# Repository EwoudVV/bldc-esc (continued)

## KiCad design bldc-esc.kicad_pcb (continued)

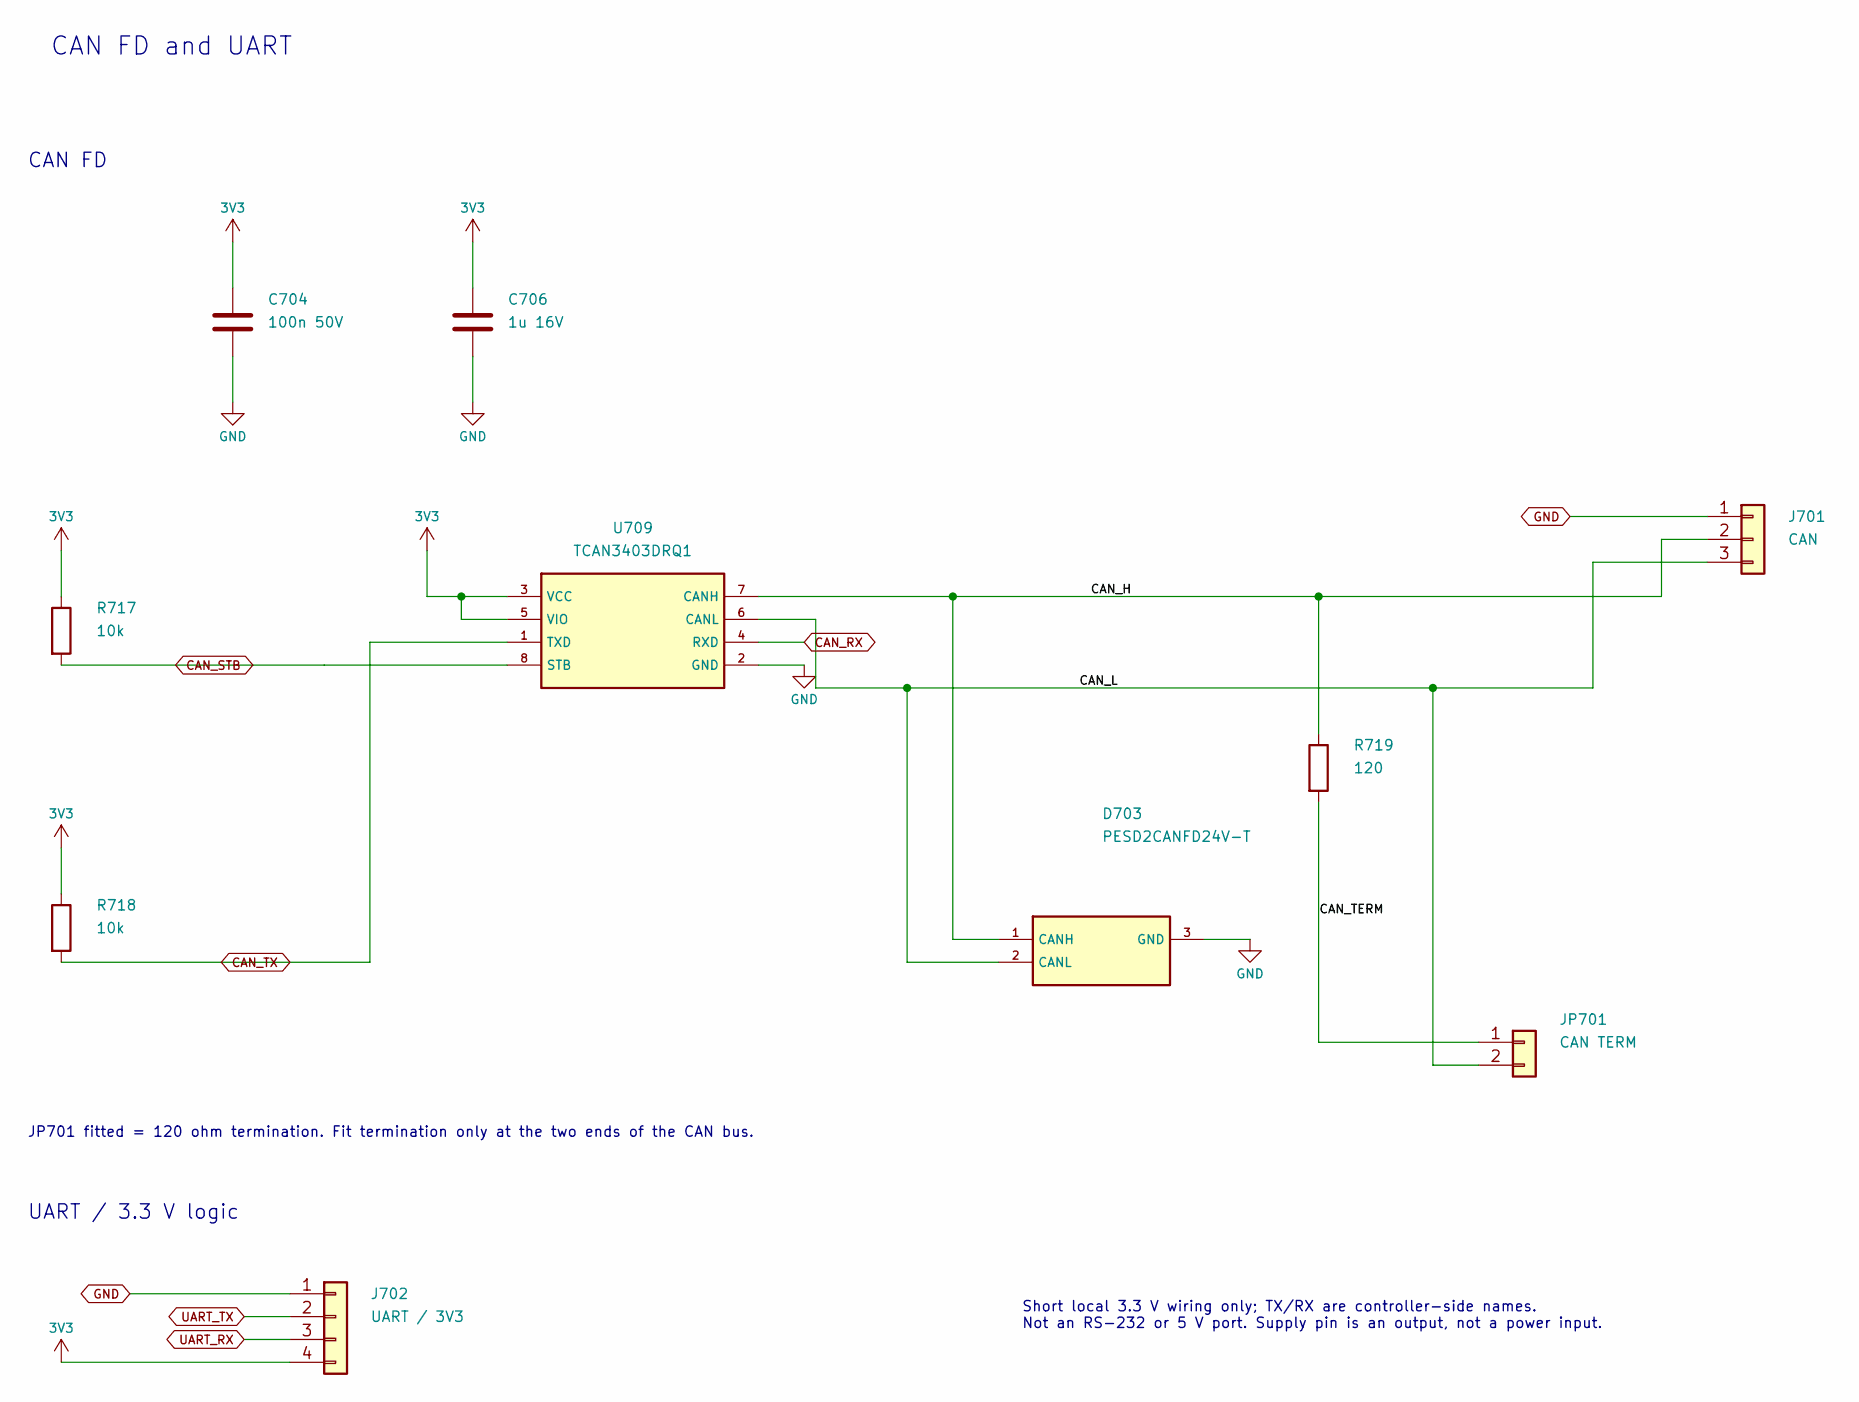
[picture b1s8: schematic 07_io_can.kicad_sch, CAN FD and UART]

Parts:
C704: 100n 50V; C_0603_1608Metric; MPN C0603C104K5RACTU
C706: 1u 16V; C_0603_1608Metric; MPN C0603C105K4RACTU
D703: PESD2CANFD24V-T; SOT-23; MPN PESD2CANFD24V-TR
J701: CAN; JST_GH_BM03B-GHS-TBT_1x03-1MP_P1.25mm_Vertical; MPN BM03B-GHS-TBT(LF)(SN)
J702: UART / 3V3; JST_GH_BM04B-GHS-TBT_1x04-1MP_P1.25mm_Vertical; MPN BM04B-GHS-TBT(LF)(SN)
JP701: CAN TERM; PinHeader_1x02_P2.54mm_Vertical; MPN M20-9990245
R717, R718: 10k; R_0603_1608Metric; MPN RC0603FR-0710KL
R719: 120; R_0805_2012Metric; MPN RC0805FR-07120RL
U709: TCAN3403DRQ1; SOIC-8_3.9x4.9mm_P1.27mm; MPN TCAN3403DRQ1

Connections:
3V3: C704.1, C706.1, J702.4, R717.1, R718.1, U709.3 (VCC), U709.5 (VIO); also elsewhere on the board
/07_io_can/CAN_H: D703.1 (CANH), J701.2, R719.1, U709.7 (CANH)
/07_io_can/CAN_L: D703.2 (CANL), J701.3, JP701.2, U709.6 (CANL)
/07_io_can/CAN_TERM: JP701.1, R719.2
CAN_RX: U709.4 (RXD); also elsewhere on the board
CAN_STB: R717.2, U709.8 (STB); also elsewhere on the board
CAN_TX: R718.2, U709.1 (TXD); also elsewhere on the board
UART_RX: J702.3; also elsewhere on the board
UART_TX: J702.2; also elsewhere on the board

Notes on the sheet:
CAN FD and UART
CAN FD
JP701 fitted = 120 ohm termination. Fit termination only at the two ends of the CAN bus.
UART / 3.3 V logic
Short local 3.3 V wiring only; TX/RX are controller-side names. Not an RS-232 or 5 V port. Supply pin is an output, not a power input.

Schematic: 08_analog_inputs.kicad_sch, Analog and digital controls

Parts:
C845, C847: 100n 50V; C_0603_1608Metric; MPN C0603C104K5RACTU
C850, C855: 10n 50V; C_0603_1608Metric; MPN C0603C103K5RACTU
C852, C857, C865, C868, C871: 1n 50V; C_0603_1608Metric; MPN C0603C102J5GACTU
D850, D855: BAV199; SOT-23; MPN BAV199,215
D852, D857, D865, D868, D871: PESD5V0S1BA; D_SOD-323; MPN PESD5V0S1BA,115
J801: THROTTLE_ADC; JST_GH_BM03B-GHS-TBT_1x03-1MP_P1.25mm_Vertical; MPN BM03B-GHS-TBT(LF)(SN)
J802: AUX_ANALOG_ADC; JST_GH_BM03B-GHS-TBT_1x03-1MP_P1.25mm_Vertical; MPN BM03B-GHS-TBT(LF)(SN)
J803: RC PWM; JST_GH_BM03B-GHS-TBT_1x03-1MP_P1.25mm_Vertical; MPN BM03B-GHS-TBT(LF)(SN)
J804: BRAKE / DIR; JST_GH_BM03B-GHS-TBT_1x03-1MP_P1.25mm_Vertical; MPN BM03B-GHS-TBT(LF)(SN)
R850, R855: 12.1k; R_0603_1608Metric; MPN RC0603FR-0712K1L
R851, R856, R866, R869, R872: 10k; R_0603_1608Metric; MPN RC0603FR-0710KL
R852, R857: 100; R_0603_1608Metric; MPN RC0603FR-07100RL
R865, R868, R871: 1k; R_0603_1608Metric; MPN RC0603FR-071KL
U802: SN74LVC3G17DCTR; SSOP-8_2.95x2.8mm_P0.65mm; MPN SN74LVC3G17DCTR
U803: TLV9062IDR; SOIC-8_3.9x4.9mm_P1.27mm; MPN TLV9062IDR

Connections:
3V3: C845.1, R869.1, R872.1, U802.8 (VCC); also elsewhere on the board
3V3_A: C847.1, D850.2 (K), D855.2 (K), U803.8 (V+); also elsewhere on the board
5V_HALL: J801.1, J802.1, J803.2; also elsewhere on the board
/08_analog_inputs/AUX_ANALOG_ADC_BUF: R857.1, U803.6 (-), U803.7
/08_analog_inputs/AUX_ANALOG_ADC_DIV: C855.1, D855.3 (common), R855.2, R856.1, U803.5 (+)
/08_analog_inputs/RC_PWM_RAW_FILT: C865.1, R865.2, U802.1
/08_analog_inputs/THROTTLE_ADC_BUF: R852.1, U803.1, U803.2 (-)
/08_analog_inputs/THROTTLE_ADC_DIV: C850.1, D850.3 (common), R850.2, R851.1, U803.3 (+)
/08_analog_inputs/nBRAKE_RAW_FILT: C868.1, R868.2, U802.3
/08_analog_inputs/nDIR_RAW_FILT: C871.1, R871.2, U802.6
AUX_ANALOG_ADC: C857.1, R857.2; also elsewhere on the board
RC_PWM_IN: U802.7; also elsewhere on the board
THROTTLE_ADC: C852.1, R852.2; also elsewhere on the board
nBRAKE_IN: U802.5; also elsewhere on the board
nDIR_IN: U802.2; also elsewhere on the board

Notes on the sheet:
Analog and digital controls
Analog controls / 0-5 V input
Digital controls / 3.3 or 5 V logic

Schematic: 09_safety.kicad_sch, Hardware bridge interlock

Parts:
C711, C712, C713, C714, C715, C716, C719, C720: 100n 50V; C_0603_1608Metric; MPN C0603C104K5RACTU
R705, R707, R708, R716, R724, R725: 100k; R_0603_1608Metric; MPN RC0603FR-07100KL
R706, R710, R711, R712, R713, R714, R715, R723: 10k; R_0603_1608Metric; MPN RC0603FR-0710KL
R709: 1k; R_0603_1608Metric; MPN RC0603FR-071KL
U703, U704, U707, U708, U711, U712: SN74LVC1G11DBVR; SOT-23-6; MPN SN74LVC1G11DBVR
U705: SN74LVC1G74DCTR; SSOP-8_2.95x2.8mm_P0.65mm; MPN SN74LVC1G74DCTR
U706: SN74LVC244APWR; TSSOP-20_4.4x6.5mm_P0.65mm; MPN SN74LVC244APWR

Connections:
3V3: C711.1, C712.1, C713.1, C714.1, C715.1, C716.1, C719.1, C720.1, R706.1, U703.5 (VCC), U704.5 (VCC), U705.2 (D), U705.7 (nPRE), U705.8 (VCC), U706.20 (VCC), U707.5 (VCC), U708.5 (VCC), U711.5 (VCC), U712.5 (VCC); also elsewhere on the board
/09_safety/DRV_ENABLE_PRE: U707.4, U712.1
/09_safety/SAFETY_GOOD: U704.4, U705.6 (nCLR)
/09_safety/SYSTEM_GOOD: U704.1, U711.4
/09_safety/SYSTEM_GOOD_PRE: U703.4, U711.1
/09_safety/nFAULT_LATCH: R709.1, U705.5 (Q), U708.6
/09_safety/nPWM_ENABLE: R706.2, U705.3 (nQ), U706.1 (nOE1), U706.19 (nOE2)
BRIDGE_ARM_REQ: R705.1, U705.1 (CLK); also elsewhere on the board
BRK_ARMED: U711.6, U712.6; also elsewhere on the board
BUS_OK: R708.1, U703.3, U707.6; also elsewhere on the board
BUS_OK_SENSE: R708.2; also elsewhere on the board
DRV_ENABLE: U712.4; also elsewhere on the board
DRV_WAKE_REQ: R716.1, U707.1; also elsewhere on the board
DRV_nFAULT: R725.1, U704.6; also elsewhere on the board
DRV_nFAULT_SENSE: R725.2; also elsewhere on the board
DUMP_PWM: U708.1; also elsewhere on the board
DUMP_PWM_SAFE: U708.4; also elsewhere on the board
HW_ENABLE_OK: U703.6; also elsewhere on the board
IN_AH: R710.1, U706.18 (Y1); also elsewhere on the board
IN_AL: R711.1, U706.16 (Y2); also elsewhere on the board
IN_BH: R712.1, U706.14 (Y3); also elsewhere on the board
IN_BL: R713.1, U706.12 (Y4); also elsewhere on the board
IN_CH: R714.1, U706.9 (Y5); also elsewhere on the board
IN_CL: R715.1, U706.7 (Y6); also elsewhere on the board
NRST: U703.1, U707.3, U708.3; also elsewhere on the board
PWM_AH: U706.2 (A1); also elsewhere on the board
PWM_AL: U706.4 (A2); also elsewhere on the board
PWM_BH: U706.6 (A3); also elsewhere on the board
PWM_BL: U706.8 (A4); also elsewhere on the board
PWM_CH: U706.11 (A5); also elsewhere on the board
PWM_CL: U706.13 (A6); also elsewhere on the board
WD_RUN: R723.1, U711.3, U712.3; also elsewhere on the board
WD_RUN_SENSE: R723.2; also elsewhere on the board
nFAULT_LATCH_SENSE: R709.2; also elsewhere on the board
nHW_ENABLE_FILT: R724.1; also elsewhere on the board
nHW_ENABLE_SENSE: R724.2; also elsewhere on the board
nOC_HW: R707.1, U704.3; also elsewhere on the board
nOC_HW_SENSE: R707.2; also elsewhere on the board

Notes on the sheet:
Hardware bridge interlock
Arm interlock / fault removal does not re-arm the bridge
Driver wake / independent chopper request
MCU monitoring / series isolation
Hardware fault and enable nodes are isolated from MCU GPIO drive. Disable UCPD dead-battery control before reading PB4.

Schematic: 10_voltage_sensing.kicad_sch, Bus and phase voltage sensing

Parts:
C801, C811, C821, C831: 220p 50V; C_0603_1608Metric; MPN C0603C221J5GACTU
C802, C812, C822, C832: 1n 50V; C_0603_1608Metric; MPN C0603C102J5GACTU
C840: 100n 50V; C_0603_1608Metric; MPN C0603C104K5RACTU
D801, D811, D821, D831: BAV199; SOT-23; MPN BAV199,215
R801, R802, R811, R812, R821, R822, R831, R832: 100k 0.1%; R_0603_1608Metric; MPN RT0603BRD07100KL
R803, R813, R823, R833: 10k 0.1%; R_0603_1608Metric; MPN RT0603BRD0710KL
R804, R814, R824, R834: 100; R_0603_1608Metric; MPN RC0603FR-07100RL
U801: TLV9064IPWR; TSSOP-14_4.4x5mm_P0.65mm; MPN TLV9064IPWR

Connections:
3V3_A: C840.1, D801.2 (K), D811.2 (K), D821.2 (K), D831.2 (K), U801.4 (V+); also elsewhere on the board
/10_voltage_sensing/V_BUS_ADC_BUF: R804.1, U801.1, U801.2 (-)
/10_voltage_sensing/V_BUS_ADC_DIV: C801.1, D801.3 (common), R802.2, R803.1, U801.3 (+)
/10_voltage_sensing/V_BUS_ADC_MID: R801.2, R802.1
/10_voltage_sensing/V_PHASE_A_BUF: R814.1, U801.6 (-), U801.7
/10_voltage_sensing/V_PHASE_A_DIV: C811.1, D811.3 (common), R812.2, R813.1, U801.5 (+)
/10_voltage_sensing/V_PHASE_A_MID: R811.2, R812.1
/10_voltage_sensing/V_PHASE_B_BUF: R824.1, U801.8, U801.9 (-)
/10_voltage_sensing/V_PHASE_B_DIV: C821.1, D821.3 (common), R822.2, R823.1, U801.10 (+)
/10_voltage_sensing/V_PHASE_B_MID: R821.2, R822.1
/10_voltage_sensing/V_PHASE_C_BUF: R834.1, U801.13 (-), U801.14
/10_voltage_sensing/V_PHASE_C_DIV: C831.1, D831.3 (common), R832.2, R833.1, U801.12 (+)
/10_voltage_sensing/V_PHASE_C_MID: R831.2, R832.1
PHASE_A: R811.1; also elsewhere on the board
PHASE_B: R821.1; also elsewhere on the board
PHASE_C: R831.1; also elsewhere on the board
VBUS: R801.1; also elsewhere on the board
V_BUS_ADC: C802.1, R804.2; also elsewhere on the board
V_PHASE_A: C812.1, R814.2; also elsewhere on the board
V_PHASE_B: C822.1, R824.2; also elsewhere on the board
V_PHASE_C: C832.1, R834.2; also elsewhere on the board

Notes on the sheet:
Bus and phase voltage sensing
Bus voltage
Phase A voltage
Phase B voltage
Phase C voltage
21:1 dividers; 2.5 V ADC full scale = 52.5 V at the input. Buffers isolate the dividers from ADC sampling transients. Normal operation remains limited to a 12-30 V bus.

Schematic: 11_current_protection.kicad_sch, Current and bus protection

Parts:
C110, C111, C112, C117: 10n 50V; C_0603_1608Metric; MPN C0603C103K5RACTU
C113, C114: 100n 50V; C_0603_1608Metric; MPN C0603C104K5RACTU
R110, R113, R114, R119: 10k 0.1%; R_0603_1608Metric; MPN RT0603BRD0710KL
R111, R112: 90.9k 0.1%; R_0603_1608Metric; MPN RT0603BRD0790K9L
R115: 16.9k 0.1%; R_0603_1608Metric; MPN RT0603BRD0716K9L
R116: 4.7k; R_0603_1608Metric; MPN RC0603FR-074K7L
R117: 10k; R_0603_1608Metric; MPN RC0603FR-0710KL
R118: 40.2k 0.1%; R_0603_1608Metric; MPN RT0603BRD0740K2L
U101, U102: TLV9024PWR; TSSOP-14_4.4x5mm_P0.65mm; MPN TLV9024PWR

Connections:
3V3: R116.1, R117.1; also elsewhere on the board
3V3_A: C113.1, C114.1, U101.3 (V+), U102.3 (V+); also elsewhere on the board
/11_current_protection/BUS_OV_REF: C112.1, R114.2, R115.1, U102.9 (+)
/11_current_protection/BUS_UV_REF: C117.1, R118.2, R119.1, U102.10 (-)
/11_current_protection/OC_HI: C110.1, R110.2, R111.1, U101.5 (+), U101.9 (+), U102.5 (+)
/11_current_protection/OC_LO: C111.1, R112.2, R113.1, U101.6 (-), U101.10 (-), U102.6 (-)
BUS_OK: R117.2, U102.13, U102.14; also elsewhere on the board
I_PHASE_A: U101.4 (-), U101.7 (+); also elsewhere on the board
I_PHASE_B: U101.8 (-), U101.11 (+); also elsewhere on the board
I_PHASE_C: U102.4 (-), U102.7 (+); also elsewhere on the board
VREF_2V5: R110.1, R112.1, R114.1, R118.1; also elsewhere on the board
V_BUS_ADC: U102.8 (-), U102.11 (+); also elsewhere on the board
nOC_HW: R116.2, U101.1, U101.2, U101.13, U101.14, U102.1, U102.2; also elsewhere on the board

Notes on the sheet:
Current and bus protection
Bipolar phase-current window
Phase A / upper
Phase A / lower
Phase B / upper
Phase B / lower
Phase C / upper
Phase C / lower
Current thresholds / about +/-50 A
Board protection only. Use lower motor limits. OEM motor: 0.75 A.
Bus window / about 10.5-33 V

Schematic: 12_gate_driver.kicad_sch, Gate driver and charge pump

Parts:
C201: 22u 63V; CP_Radial_D6.3mm_P2.50mm; MPN EEUFC1J220
C202: 100n 100V; C_0603_1608Metric; MPN C0603C104K1RACTU
C203: 47n 100V; C_0805_2012Metric; MPN C0805C473K1RACTU
C204: 1u 50V; C_1206_3216Metric; MPN C3216X7R1H105K160AB
C205: 1u 25V; C_0805_2012Metric; MPN C0805C105K3RACTU
C206: 1u 16V; C_0603_1608Metric; MPN C0603C105K4RACTU
C207: 100n 50V; C_0603_1608Metric; MPN C0603C104K5RACTU
R201: 2.2; R_0805_2012Metric; MPN RC0805FR-072R2L
R202: 4.7k; R_0603_1608Metric; MPN RC0603FR-074K7L
R203, R205: 10k; R_0603_1608Metric; MPN RC0603FR-0710KL
R204: 100k; R_0603_1608Metric; MPN RC0603FR-07100KL
U201: DRV8353SRTAT; DRV8353_RTA0040B; MPN DRV8353SRTAT

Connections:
3V3: R202.1, R203.1, R205.1; also elsewhere on the board
3V3_A: C207.1, U201.24 (VREF); also elsewhere on the board
/12_gate_driver/DRV_CPH: C203.1, U201.2 (CPH)
/12_gate_driver/DRV_CPL: C203.2, U201.1 (CPL)
/12_gate_driver/DRV_DVDD: C206.1, U201.38 (DVDD)
/12_gate_driver/DRV_VCP: C204.1, U201.5 (VCP)
/12_gate_driver/DRV_VGLS: C205.1, U201.40 (VGLS)
/12_gate_driver/DRV_VM: C201.1, C202.1, R201.2, U201.3 (VM)
DRV_ENABLE: R204.1, U201.31 (ENABLE); also elsewhere on the board
DRV_SCK: U201.29 (SCLK); also elsewhere on the board
DRV_SDI: U201.28 (SDI); also elsewhere on the board
DRV_SDO: R202.2, U201.27 (SDO); also elsewhere on the board
DRV_nCS: R205.2, U201.30 (nSCS); also elsewhere on the board
DRV_nFAULT: R203.2, U201.26 (nFAULT); also elsewhere on the board
GHA_DRV: U201.6 (GHA); also elsewhere on the board
GHB_DRV: U201.15 (GHB); also elsewhere on the board
GHC_DRV: U201.16 (GHC); also elsewhere on the board
GLA_DRV: U201.8 (GLA); also elsewhere on the board
GLB_DRV: U201.13 (GLB); also elsewhere on the board
GLC_DRV: U201.18 (GLC); also elsewhere on the board
IN_AH: U201.32 (INHA); also elsewhere on the board
IN_AL: U201.33 (INLA); also elsewhere on the board
IN_BH: U201.34 (INHB); also elsewhere on the board
IN_BL: U201.35 (INLB); also elsewhere on the board
IN_CH: U201.36 (INHC); also elsewhere on the board
IN_CL: U201.37 (INLC); also elsewhere on the board
KS_A_N: U201.10 (SNA); also elsewhere on the board
KS_B_N: U201.11 (SNB); also elsewhere on the board
KS_C_N: U201.20 (SNC); also elsewhere on the board
PHASE_A: U201.7 (SHA); also elsewhere on the board
PHASE_B: U201.14 (SHB); also elsewhere on the board
PHASE_C: U201.17 (SHC); also elsewhere on the board
SOURCE_A: U201.9 (SPA); also elsewhere on the board
SOURCE_B: U201.12 (SPB); also elsewhere on the board
SOURCE_C: U201.19 (SPC); also elsewhere on the board
SO_A_DRV: U201.23 (SOA); also elsewhere on the board
SO_B_DRV: U201.22 (SOB); also elsewhere on the board
SO_C_DRV: U201.21 (SOC); also elsewhere on the board
VBUS: C204.2, R201.1, U201.4 (VDRAIN); also elsewhere on the board

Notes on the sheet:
Gate driver and charge pump
Gate driver / charge pump
VM filter and pump capacitors belong next to U201. VCP reservoir returns to VBUS, not GND.
SPx returns directly to each low-side source. SNx / CSA inputs use Kelvin shunt sense pads.
Six PWM inputs arrive through the hardware arm interlock. ENABLE is separate for driver setup.

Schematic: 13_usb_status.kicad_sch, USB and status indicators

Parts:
C413: 100n 50V; C_0603_1608Metric; MPN C0603C104K5RACTU
D511: STATUS; LED_0603_1608Metric; MPN LTST-C190KGKT
D512: COMM; LED_0603_1608Metric; MPN LTST-C190KGKT
D513: POWER; LED_0603_1608Metric; MPN LTST-C190KGKT
F401: 0.5A / 6V; MF_PSMF0805; MPN MF-PSMF050X-2
J401: USB4105-GF-A; USB4105_PCBWay; MPN USB4105-GF-A
R411, R412: 5.1k; R_0603_1608Metric; MPN RC0603FR-075K1L
R413, R414: 22; R_0603_1608Metric; MPN RC0603FR-0722RL
R415: 10k; R_0603_1608Metric; MPN RC0603FR-0710KL
R416: 15k; R_0603_1608Metric; MPN RC0603FR-0715KL
R511, R512, R513: 1k; R_0603_1608Metric; MPN RC0603FR-071KL
TP401: 5V_BUS; TestPoint_Pad_D1.5mm; MPN TESTPOINT
TP402: 5V_SYS; TestPoint_Pad_D1.5mm; MPN TESTPOINT
TP403: 3V3; TestPoint_Pad_D1.5mm; MPN TESTPOINT
TP404: GND; TestPoint_Pad_D1.5mm; MPN TESTPOINT
U404: USBLC6-2SC6; SOT-23-6; MPN USBLC6-2SC6

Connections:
3V3: R513.1, TP403.1 (1_1); also elsewhere on the board
5V_BUS: TP401.1 (1_1); also elsewhere on the board
5V_SYS: TP402.1 (1_1); also elsewhere on the board
/13_usb_status/CC1: J401.A5 (CC1), R411.1
/13_usb_status/CC2: J401.B5 (CC2), R412.1
/13_usb_status/LED_1: D511.2 (A), R511.2
/13_usb_status/LED_2: D512.2 (A), R512.2
/13_usb_status/LED_3: D513.2 (A), R513.2
/13_usb_status/USB_DM_ESD: R414.1, U404.4 (I/O2)
/13_usb_status/USB_DM_PORT: J401.A7 (D-), J401.B7 (D-), U404.3 (I/O2)
/13_usb_status/USB_DP_ESD: R413.1, U404.6 (I/O1)
/13_usb_status/USB_DP_PORT: J401.A6 (D+), J401.B6 (D+), U404.1 (I/O1)
/13_usb_status/USB_VBUS_RAW: C413.1, F401.1, J401.A4 (VBUS), J401.A9 (VBUS), J401.B4 (VBUS), J401.B9 (VBUS), R415.1, U404.5 (VBUS)
CHASSIS: J401.SH (SHIELD); also elsewhere on the board
LED_COMM: R512.1; also elsewhere on the board
LED_STATUS: R511.1; also elsewhere on the board
USB_DM: R414.2; also elsewhere on the board
USB_DP: R413.2; also elsewhere on the board
USB_VBUS_SENSE: R415.2, R416.1; also elsewhere on the board

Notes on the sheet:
USB and status indicators
USB-C device port
Status / probe points
USB shield bonds to CHASSIS. D+/D- protection belongs close to the connector; 22 ohm resistors belong near the MCU.

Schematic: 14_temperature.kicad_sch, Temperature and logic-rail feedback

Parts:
C848: 100n 50V; C_0603_1608Metric; MPN C0603C104K5RACTU
C880, C883, C886, C889, C899: 10n 50V; C_0603_1608Metric; MPN C0603C103K5RACTU
C888, C891: 1n 50V; C_0603_1608Metric; MPN C0603C102J5GACTU
D886, D889: BAV199; SOT-23; MPN BAV199,215
D888, D891: PESD5V0S1BA; D_SOD-323; MPN PESD5V0S1BA,115
J805: NTC_MOTOR; JST_GH_BM02B-GHS-TBT_1x02-1MP_P1.25mm_Vertical; MPN BM02B-GHS-TBT(LF)(SN)
J806: NTC_DUMP; JST_GH_BM02B-GHS-TBT_1x02-1MP_P1.25mm_Vertical; MPN BM02B-GHS-TBT(LF)(SN)
R880, R883, R886, R889, R898, R899: 10k 0.1%; R_0603_1608Metric; MPN RT0603BRD0710KL
R887, R890: 1k; R_0603_1608Metric; MPN RC0603FR-071KL
R888, R891: 100; R_0603_1608Metric; MPN RC0603FR-07100RL
TH801, TH802: 10k / B25-50=3380K; R_0603_1608Metric; MPN NCP18XH103F03RB
U804: TLV9062IDR; SOIC-8_3.9x4.9mm_P1.27mm; MPN TLV9062IDR

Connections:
3V3: R898.1; also elsewhere on the board
3V3_A: C848.1, D886.2 (K), D889.2 (K), U804.8 (V+); also elsewhere on the board
/14_temperature/NTC_DUMP_BUF: R891.1, U804.6 (-), U804.7
/14_temperature/NTC_DUMP_DIV: C889.1, D889.3 (common), R889.2, R890.2, U804.5 (+)
/14_temperature/NTC_MOTOR_BUF: R888.1, U804.1, U804.2 (-)
/14_temperature/NTC_MOTOR_DIV: C886.1, D886.3 (common), R886.2, R887.2, U804.3 (+)
NTC_BRIDGE: C880.1, R880.2, TH801.1; also elsewhere on the board
NTC_DUMP: C891.1, R891.2; also elsewhere on the board
NTC_MOTOR: C888.1, R888.2; also elsewhere on the board
NTC_PCB: C883.1, R883.2, TH802.1; also elsewhere on the board
VREF_2V5: R880.1, R883.1, R886.1, R889.1; also elsewhere on the board
V_3V3_ADC: C899.1, R898.2, R899.1; also elsewhere on the board

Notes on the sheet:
Temperature and logic-rail feedback
Temperature feedback
TH801/TH802: 10k, B25/50=3380 K. External NTC conversion must subtract the 1k series resistor. External channels are buffered; configure their actual R/T curves before thermal-limit testing.

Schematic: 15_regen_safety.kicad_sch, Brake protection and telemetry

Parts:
C307, C309, C311: 100n 50V; C_0603_1608Metric; MPN C0603C104K5RACTU
C308: 1n 50V; C_0603_1608Metric; MPN C0603C102J5GACTU
C310: 10n 50V; C_0603_1608Metric; MPN C0603C103K5RACTU
C312: 100p 50V; C_0603_1608Metric; MPN C0603C101J5GACTU
D302, D303: BAT54H; D_SOD-123F; MPN BAT54H,115
R311, R312, R313: 10k; R_0603_1608Metric; MPN RC0603FR-0710KL
R314, R315, R317: 100k; R_0603_1608Metric; MPN RC0603FR-07100KL
R316, R318: 150k; R_0603_1608Metric; MPN RC0603FR-07150KL
R320: 10k 0.1%; R_0603_1608Metric; MPN RT0603BRD0710KL
R321: 15k 0.1%; R_0603_1608Metric; MPN RT0603BRD0715KL
U304: TLV3201AIDBVR; SOT-23-5; MPN TLV3201AIDBVR
U305: TPS3808G50DBVR; SOT-23-6; MPN TPS3808G50DBVR
U306: SN74LVC1G17DBVR; SOT-23-5; MPN SN74LVC1G17DBVR
U307: SN74LVC1G74DCTR; SSOP-8_2.95x2.8mm_P0.65mm; MPN SN74LVC1G74DCTR

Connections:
5V_BUS: C307.1, C309.1, C311.1, R311.1, R312.1, U304.5 (V+), U305.3 (nMR), U305.5 (SENSE), U305.6 (VDD), U306.5 (VCC), U307.2 (D), U307.7 (nPRE), U307.8 (VCC); also elsewhere on the board
/15_regen_safety/BRK_CLEAR: D302.2 (A), D303.2 (A), R311.2, U307.6 (nCLR)
/15_regen_safety/BRK_CLK: U306.4, U307.1 (CLK)
/15_regen_safety/BRK_CLK_RC: C310.1, R313.2, U306.2
/15_regen_safety/BRK_CT: C308.1, U305.4 (CT)
/15_regen_safety/BRK_OC_OK: D303.1 (K), U304.1 (OUT)
/15_regen_safety/BRK_POR: D302.1 (K), R312.2, R313.1, U305.1 (nRESET)
/15_regen_safety/nBRK_ARMED: R317.1, U307.3 (nQ)
BRK_ARMED: R314.1, U307.5 (Q); also elsewhere on the board
BRK_FAULT_SENSE: R317.2, R318.1; also elsewhere on the board
DUMP_ACTIVE_SENSE: R315.2, R316.1; also elsewhere on the board
DUMP_CURRENT: R320.1, U304.4 (IN-); also elsewhere on the board
DUMP_I_ADC: C312.1, R320.2, R321.1; also elsewhere on the board
DUMP_REF: U304.3 (IN+); also elsewhere on the board
nDUMP_REQUEST: R315.1; also elsewhere on the board

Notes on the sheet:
Brake protection and telemetry
5 V-to-3.3 V monitor dividers
Dump current: 36 mV/A to PA6 ADC2_IN3. Use a long regular ADC acquisition time.
Chopper overcurrent trip and power-cycle latch

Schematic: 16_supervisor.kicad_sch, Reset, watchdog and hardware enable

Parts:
C701, C703, C717, C718: 100n 50V; C_0603_1608Metric; MPN C0603C104K5RACTU
C702: 47n 50V; C_0603_1608Metric; MPN C0603C473K5RACTU
C705: 10n 50V; C_0603_1608Metric; MPN C0603C103K5RACTU
D704: PESD5V0S1BA; D_SOD-323; MPN PESD5V0S1BA,115
J703: HW ENABLE; PinHeader_1x02_P2.54mm_Vertical; MPN M20-9990245
JP704: RUN 1-2 / SERVICE 2-3; PinHeader_1x03_P2.54mm_Vertical; MPN M20-9990345
R701, R703: 0; R_0603_1608Metric; MPN RC0603JR-070RL
R702, R720, R722: 10k; R_0603_1608Metric; MPN RC0603FR-0710KL
R704: 100k; R_0603_1608Metric; MPN RC0603FR-07100KL
R721: 1k; R_0603_1608Metric; MPN RC0603FR-071KL
U701: TPS389033DSER; WSON-6_1.5x1.5mm_P0.5mm; MPN TPS389033DSER
U702: TPS3431SDRBR; VSON-8-1EP_3x3mm_P0.65mm_EP1.65x2.4mm; MPN TPS3431SDRBR
U710: SN74LVC1G14DBVR; SOT-23-5; MPN SN74LVC1G14DBVR

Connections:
3V3: C701.1, C703.1, C717.1, C718.1, JP704.1, R702.1, R720.1, R722.1, U701.3 (nMR), U701.4 (VDD), U702.1 (VDD), U702.3 (EN), U710.5 (VCC); also elsewhere on the board
3V3_A: U701.1 (SENSE); also elsewhere on the board
/16_supervisor/POR_CT: C702.1, U701.5 (CT)
/16_supervisor/POWER_OK: R701.2, U701.6 (nRESET)
/16_supervisor/WD_CWD: R702.2, U702.2 (CWD)
/16_supervisor/WD_OK: R703.2, U702.7 (nWDO)
HW_ENABLE_OK: U710.4; also elsewhere on the board
NRST: R701.1, R703.1; also elsewhere on the board
WD_HEARTBEAT: R704.1, U702.6 (WDI); also elsewhere on the board
WD_RUN: JP704.2, R722.2, U702.5 (SET1); also elsewhere on the board
nHW_ENABLE_FILT: C705.1, R721.2, U710.2; also elsewhere on the board

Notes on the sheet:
Reset, watchdog and hardware enable
Power-on reset and watchdog
Open-drain reset outputs share NRST through zero-ohm links. R504 on the MCU sheet provides the pull-up.
Service and hardware enable
RUN 1-2 / SERVICE 2-3. SERVICE or a chopper fault forces both driver-enable and bridge-arm paths off.

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
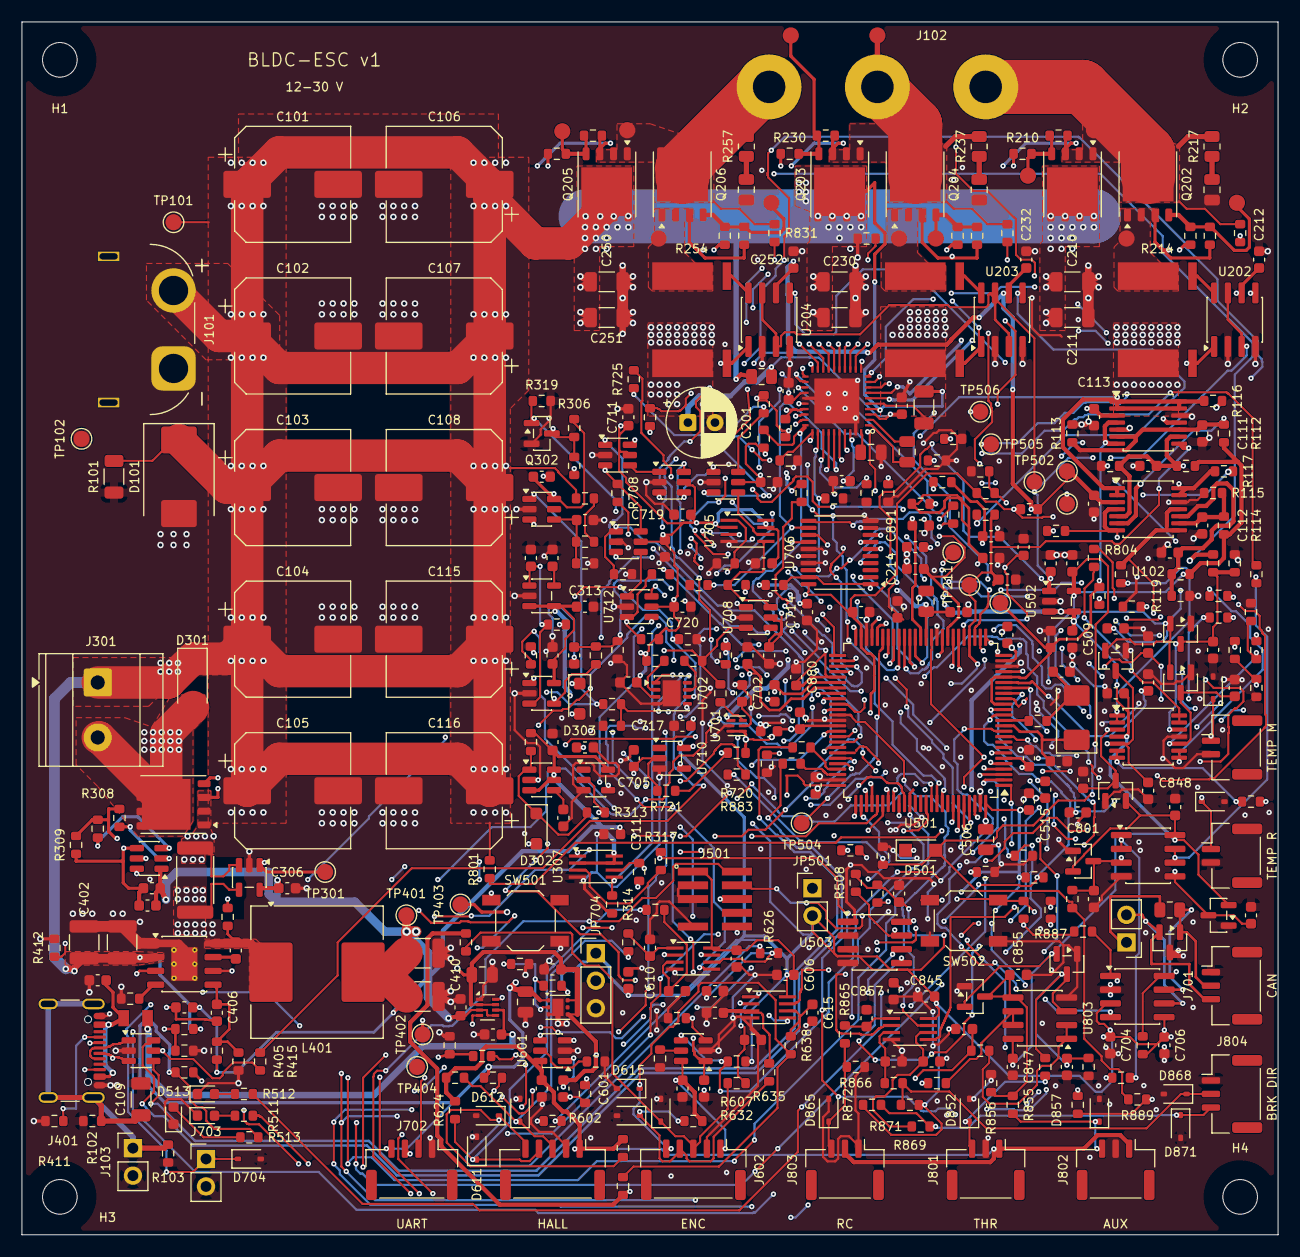
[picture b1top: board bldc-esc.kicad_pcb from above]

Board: 4 copper layers, 116.0 x 112.0 mm, 453 parts (0 on the bottom side), 245 nets.

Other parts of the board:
H1, H2, H3, H4: MountingHole_3.2mm_M3

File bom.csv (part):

reference,sheet,value,MPN,manufacturer,footprint,DNP,exclude_from_BOM
J101,01_dc_link,XT60PW-M,XT60PW-M,AMASS,bldc-esc:XT60PW_M_Edge,false,false
D101,01_dc_link,SMCJ30A,SMCJ30A,Littelfuse,Diode_SMD:D_SMC,false,false
C101,01_dc_link,100u 63V,GXC1J101MCW1GS,Nichicon,Capacitor_SMD:CP_Elec_10x12.5,false,false
C102,01_dc_link,100u 63V,GXC1J101MCW1GS,Nichicon,Capacitor_SMD:CP_Elec_10x12.5,false,false
C103,01_dc_link,100u 63V,GXC1J101MCW1GS,Nichicon,Capacitor_SMD:CP_Elec_10x12.5,false,false
C104,01_dc_link,100u 63V,GXC1J101MCW1GS,Nichicon,Capacitor_SMD:CP_Elec_10x12.5,false,false
C105,01_dc_link,100u 63V,GXC1J101MCW1GS,Nichicon,Capacitor_SMD:CP_Elec_10x12.5,false,false
C106,01_dc_link,100u 63V,GXC1J101MCW1GS,Nichicon,Capacitor_SMD:CP_Elec_10x12.5,false,false
C107,01_dc_link,100u 63V,GXC1J101MCW1GS,Nichicon,Capacitor_SMD:CP_Elec_10x12.5,false,false
C115,01_dc_link,100u 63V,GXC1J101MCW1GS,Nichicon,Capacitor_SMD:CP_Elec_10x12.5,false,false
C108,01_dc_link,100u 63V,GXC1J101MCW1GS,Nichicon,Capacitor_SMD:CP_Elec_10x12.5,false,false
C116,01_dc_link,100u 63V,GXC1J101MCW1GS,Nichicon,Capacitor_SMD:CP_Elec_10x12.5,false,false
R101,01_dc_link,10k,RC1206FR-0710KL,Yageo,Resistor_SMD:R_1206_3216Metric,false,false
J102,01_dc_link,MT60 / 12AWG pigtail,MT60-M,AMASS,bldc-esc:MT60_Pigtail_12AWG,false,false
J103,01_dc_link,CHASSIS,M20-9990245,Harwin,Connector_PinHeader_2.54mm:PinHeader_1x02_P2.54mm_Vertical,false,false
R102,01_dc_link,1M,RC0603FR-071ML,Yageo,Resistor_SMD:R_0603_1608Metric,false,false
C109,01_dc_link,4.7n 1kV,C1206C472KDRACTU,KEMET,Capacitor_SMD:C_1206_3216Metric,false,false
R103,01_dc_link,0,RC0603JR-070RL,Yageo,Resistor_SMD:R_0603_1608Metric,true,false
TP101,01_dc_link,VBUS,TESTPOINT,,TestPoint:TestPoint_Pad_D1.5mm,false,true
TP102,01_dc_link,GND,TESTPOINT,,TestPoint:TestPoint_Pad_D1.5mm,false,true
TP103,01_dc_link,PHASE_A,TESTPOINT,,TestPoint:TestPoint_Pad_D1.5mm,false,true
TP104,01_dc_link,PHASE_B,TESTPOINT,,TestPoint:TestPoint_Pad_D1.5mm,false,true
TP105,01_dc_link,PHASE_C,TESTPOINT,,TestPoint:TestPoint_Pad_D1.5mm,false,true
U201,12_gate_driver,DRV8353SRTAT,DRV8353SRTAT,Texas Instruments,bldc-esc:DRV8353_RTA0040B,false,false
R201,12_gate_driver,2.2,RC0805FR-072R2L,Yageo,Resistor_SMD:R_0805_2012Metric,false,false
C201,12_gate_driver,22u 63V,EEUFC1J220,Panasonic,Capacitor_THT:CP_Radial_D6.3mm_P2.50mm,false,false
C202,12_gate_driver,100n 100V,C0603C104K1RACTU,KEMET,Capacitor_SMD:C_0603_1608Metric,false,false
C203,12_gate_driver,47n 100V,C0805C473K1RACTU,KEMET,Capacitor_SMD:C_0805_2012Metric,false,false
C204,12_gate_driver,1u 50V,C3216X7R1H105K160AB,TDK,Capacitor_SMD:C_1206_3216Metric,false,false
C205,12_gate_driver,1u 25V,C0805C105K3RACTU,KEMET,Capacitor_SMD:C_0805_2012Metric,false,false
C206,12_gate_driver,1u 16V,C0603C105K4RACTU,KEMET,Capacitor_SMD:C_0603_1608Metric,false,false
C207,12_gate_driver,100n 50V,C0603C104K5RACTU,KEMET,Capacitor_SMD:C_0603_1608Metric,false,false
R202,12_gate_driver,4.7k,RC0603FR-074K7L,Yageo,Resistor_SMD:R_0603_1608Metric,false,false
R203,12_gate_driver,10k,RC0603FR-0710KL,Yageo,Resistor_SMD:R_0603_1608Metric,false,false
R204,12_gate_driver,100k,RC0603FR-07100KL,Yageo,Resistor_SMD:R_0603_1608Metric,false,false
R205,12_gate_driver,10k,RC0603FR-0710KL,Yageo,Resistor_SMD:R_0603_1608Metric,false,false
Q201,02_bridge,ISC011N06LM5,ISC011N06LM5ATMA1,Infineon,Package_SON:Infineon_PG-TDSON-8_6.15x5.15mm,false,false
Q202,02_bridge,ISC011N06LM5,ISC011N06LM5ATMA1,Infineon,Package_SON:Infineon_PG-TDSON-8_6.15x5.15mm,false,false
R210,02_bridge,3.3,RC0603FR-073R3L,Yageo,Resistor_SMD:R_0603_1608Metric,false,false
R211,02_bridge,47k,RC0603FR-0747KL,Yageo,Resistor_SMD:R_0603_1608Metric,false,false
R212,02_bridge,3.3,RC0603FR-073R3L,Yageo,Resistor_SMD:R_0603_1608Metric,false,false
R213,02_bridge,47k,RC0603FR-0747KL,Yageo,Resistor_SMD:R_0603_1608Metric,false,false
R214,02_bridge,1m 1% 8W,CSS4J-4026R-1L00F,Bourns,bldc-esc:CSS4J_4026,false,false
C210,02_bridge,1u 100V,C3216X7R2A105K160AA,TDK,Capacitor_SMD:C_1206_3216Metric,false,false
C211,02_bridge,1u 100V,C3216X7R2A105K160AA,TDK,Capacitor_SMD:C_1206_3216Metric,false,false
U202,02_bridge,INA241A2IDR,INA241A2IDR,Texas Instruments,Package_SO:SOIC-8_3.9x4.9mm_P1.27mm,false,false
C212,02_bridge,100n 50V,C0603C104K5RACTU,KEMET,Capacitor_SMD:C_0603_1608Metric,false,false
R215,02_bridge,100,RC0603FR-07100RL,Yageo,Resistor_SMD:R_0603_1608Metric,false,false
C213,02_bridge,1n 50V,C0603C102J5GACTU,KEMET,Capacitor_SMD:C_0603_1608Metric,false,false
TP210,02_bridge,I_PHASE_A,TESTPOINT,,TestPoint:TestPoint_Pad_D1.5mm,false,true
R216,02_bridge,1k,RC0603FR-071KL,Yageo,Resistor_SMD:R_0603_1608Metric,false,false
C214,02_bridge,1n 50V,C0603C102J5GACTU,KEMET,Capacitor_SMD:C_0603_1608Metric,false,false
R217,02_bridge,10,RC0805FR-0710RL,Yageo,Resistor_SMD:R_0805_2012Metric,true,false
C215,02_bridge,1n 100V,C0805C102J1GACTU,KEMET,Capacitor_SMD:C_0805_2012Metric,true,false
Q203,02_bridge,ISC011N06LM5,ISC011N06LM5ATMA1,Infineon,Package_SON:Infineon_PG-TDSON-8_6.15x5.15mm,false,false
Q204,02_bridge,ISC011N06LM5,ISC011N06LM5ATMA1,Infineon,Package_SON:Infineon_PG-TDSON-8_6.15x5.15mm,false,false
R230,02_bridge,3.3,RC0603FR-073R3L,Yageo,Resistor_SMD:R_0603_1608Metric,false,false
R231,02_bridge,47k,RC0603FR-0747KL,Yageo,Resistor_SMD:R_0603_1608Metric,false,false
R232,02_bridge,3.3,RC0603FR-073R3L,Yageo,Resistor_SMD:R_0603_1608Metric,false,false
R233,02_bridge,47k,RC0603FR-0747KL,Yageo,Resistor_SMD:R_0603_1608Metric,false,false
R234,02_bridge,1m 1% 8W,CSS4J-4026R-1L00F,Bourns,bldc-esc:CSS4J_4026,false,false
C230,02_bridge,1u 100V,C3216X7R2A105K160AA,TDK,Capacitor_SMD:C_1206_3216Metric,false,false
C231,02_bridge,1u 100V,C3216X7R2A105K160AA,TDK,Capacitor_SMD:C_1206_3216Metric,false,false
U203,02_bridge,INA241A2IDR,INA241A2IDR,Texas Instruments,Package_SO:SOIC-8_3.9x4.9mm_P1.27mm,false,false
C232,02_bridge,100n 50V,C0603C104K5RACTU,KEMET,Capacitor_SMD:C_0603_1608Metric,false,false
R235,02_bridge,100,RC0603FR-07100RL,Yageo,Resistor_SMD:R_0603_1608Metric,false,false
C233,02_bridge,1n 50V,C0603C102J5GACTU,KEMET,Capacitor_SMD:C_0603_1608Metric,false,false
TP211,02_bridge,I_PHASE_B,TESTPOINT,,TestPoint:TestPoint_Pad_D1.5mm,false,true
R236,02_bridge,1k,RC0603FR-071KL,Yageo,Resistor_SMD:R_0603_1608Metric,false,false
C234,02_bridge,1n 50V,C0603C102J5GACTU,KEMET,Capacitor_SMD:C_0603_1608Metric,false,false
R237,02_bridge,10,RC0805FR-0710RL,Yageo,Resistor_SMD:R_0805_2012Metric,true,false
C235,02_bridge,1n 100V,C0805C102J1GACTU,KEMET,Capacitor_SMD:C_0805_2012Metric,true,false
Q205,02_bridge,ISC011N06LM5,ISC011N06LM5ATMA1,Infineon,Package_SON:Infineon_PG-TDSON-8_6.15x5.15mm,false,false
Q206,02_bridge,ISC011N06LM5,ISC011N06LM5ATMA1,Infineon,Package_SON:Infineon_PG-TDSON-8_6.15x5.15mm,false,false
R250,02_bridge,3.3,RC0603FR-073R3L,Yageo,Resistor_SMD:R_0603_1608Metric,false,false
R251,02_bridge,47k,RC0603FR-0747KL,Yageo,Resistor_SMD:R_0603_1608Metric,false,false
R252,02_bridge,3.3,RC0603FR-073R3L,Yageo,Resistor_SMD:R_0603_1608Metric,false,false
R253,02_bridge,47k,RC0603FR-0747KL,Yageo,Resistor_SMD:R_0603_1608Metric,false,false
R254,02_bridge,1m 1% 8W,CSS4J-4026R-1L00F,Bourns,bldc-esc:CSS4J_4026,false,false
C250,02_bridge,1u 100V,C3216X7R2A105K160AA,TDK,Capacitor_SMD:C_1206_3216Metric,false,false
C251,02_bridge,1u 100V,C3216X7R2A105K160AA,TDK,Capacitor_SMD:C_1206_3216Metric,false,false
U204,02_bridge,INA241A2IDR,INA241A2IDR,Texas Instruments,Package_SO:SOIC-8_3.9x4.9mm_P1.27mm,false,false
C252,02_bridge,100n 50V,C0603C104K5RACTU,KEMET,Capacitor_SMD:C_0603_1608Metric,false,false
R255,02_bridge,100,RC0603FR-07100RL,Yageo,Resistor_SMD:R_0603_1608Metric,false,false
C253,02_bridge,1n 50V,C0603C102J5GACTU,KEMET,Capacitor_SMD:C_0603_1608Metric,false,false
TP212,02_bridge,I_PHASE_C,TESTPOINT,,TestPoint:TestPoint_Pad_D1.5mm,false,true
R256,02_bridge,1k,RC0603FR-071KL,Yageo,Resistor_SMD:R_0603_1608Metric,false,false
C254,02_bridge,1n 50V,C0603C102J5GACTU,KEMET,Capacitor_SMD:C_0603_1608Metric,false,false
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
